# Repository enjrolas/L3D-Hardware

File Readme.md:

This repository contains all the hardware files we use to make our cubes.  It's organized in two directories 
for the two sizes of cubes we make, a 8x8x8 cube and a 16x16x16 cube.  Each directory includes the eagle files
for the baseboard that goes at the bottom of the cube, and the thin LED stick PCBs that hold the LED themselves.
The 8x8x8 cube has 64 LED sticks, and the 16x16x16 cube has a whopping 256 LED sticks.  

Electrically, the cubes are quite simple.  They're based around the popular WS2812B addressable LED and the Spark Core processor.  Our BOM
has Chinese sources, but you can also source the WS2812B LEDs from any number of sources, such as [Adafruit](https://www.adafruit.com/products/1655) and our 
friends [at Seeed Studios](http://www.seeedstudio.com/depot/WS2812B-RGB-LED-with-Integrated-Driver-Chip-10-PCs-pack-p-1675.html).
The other components are a few common passives detailed in the BOM.

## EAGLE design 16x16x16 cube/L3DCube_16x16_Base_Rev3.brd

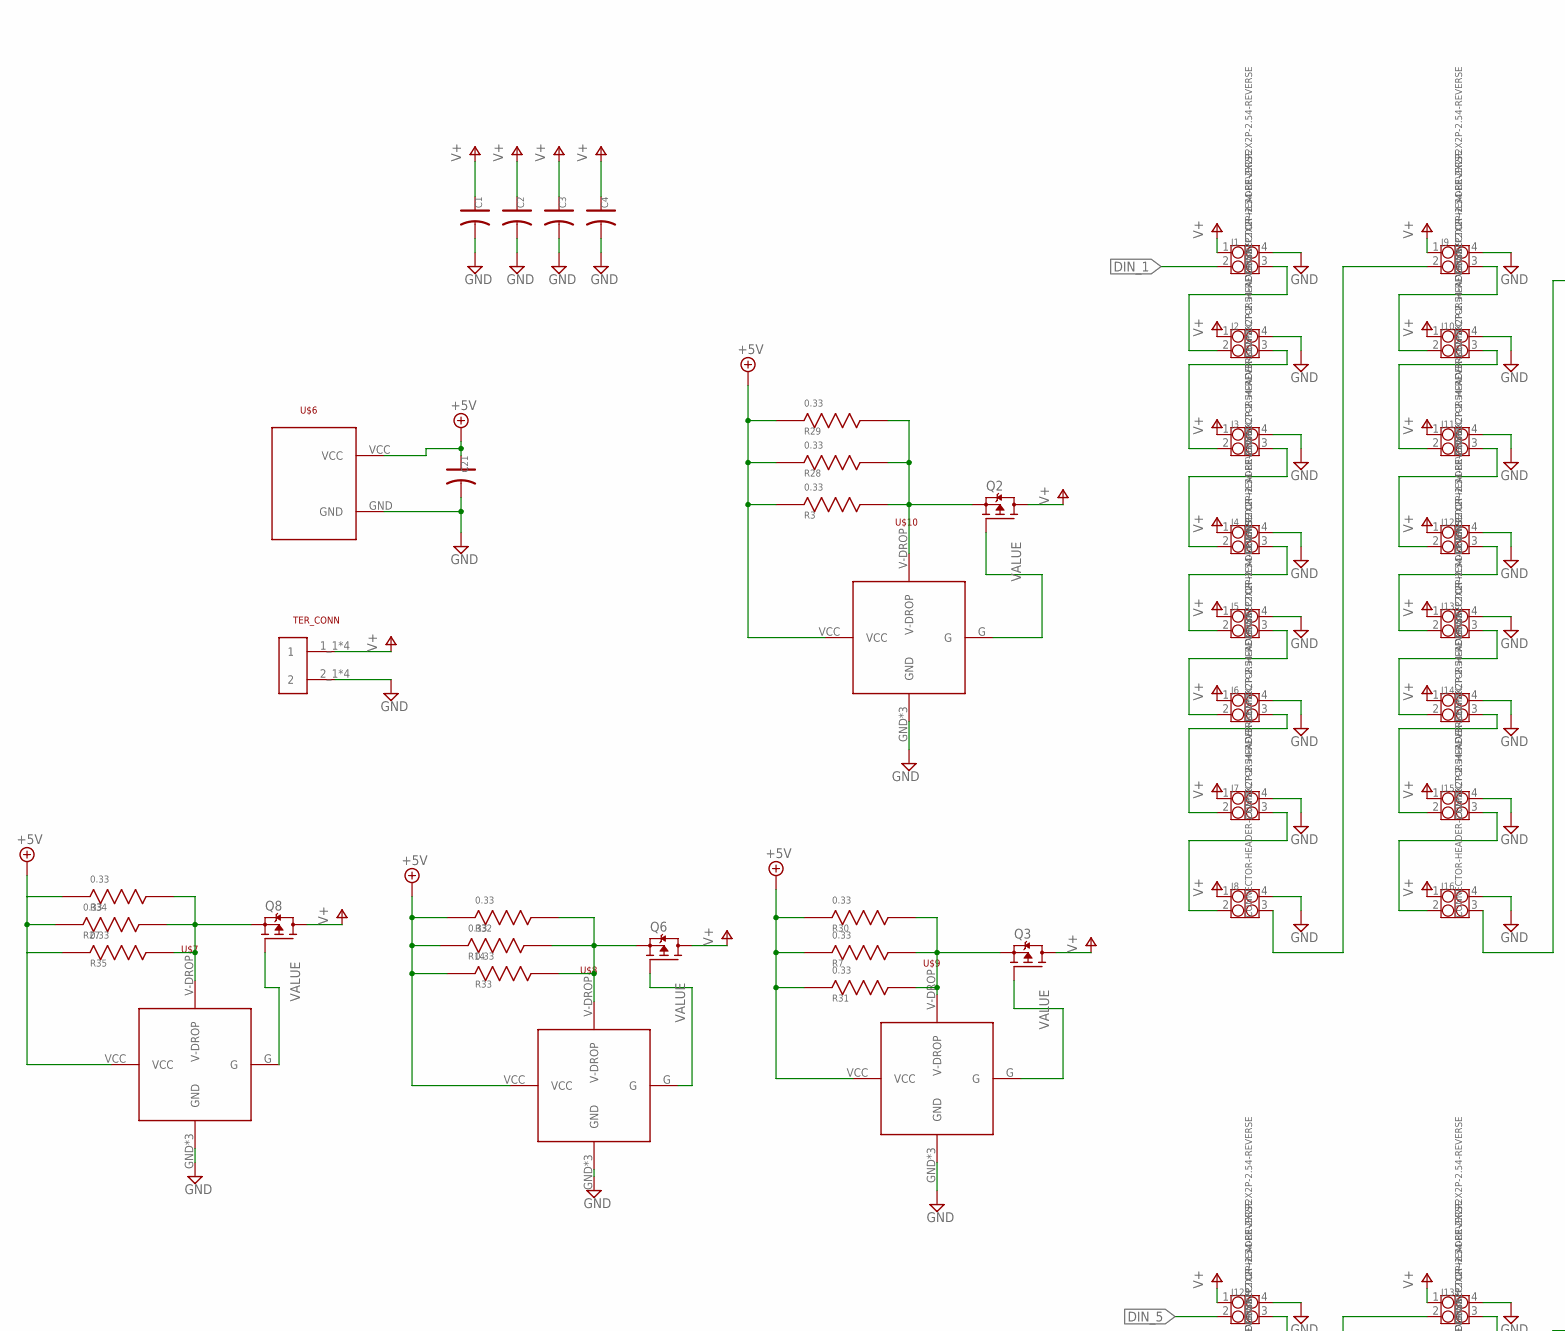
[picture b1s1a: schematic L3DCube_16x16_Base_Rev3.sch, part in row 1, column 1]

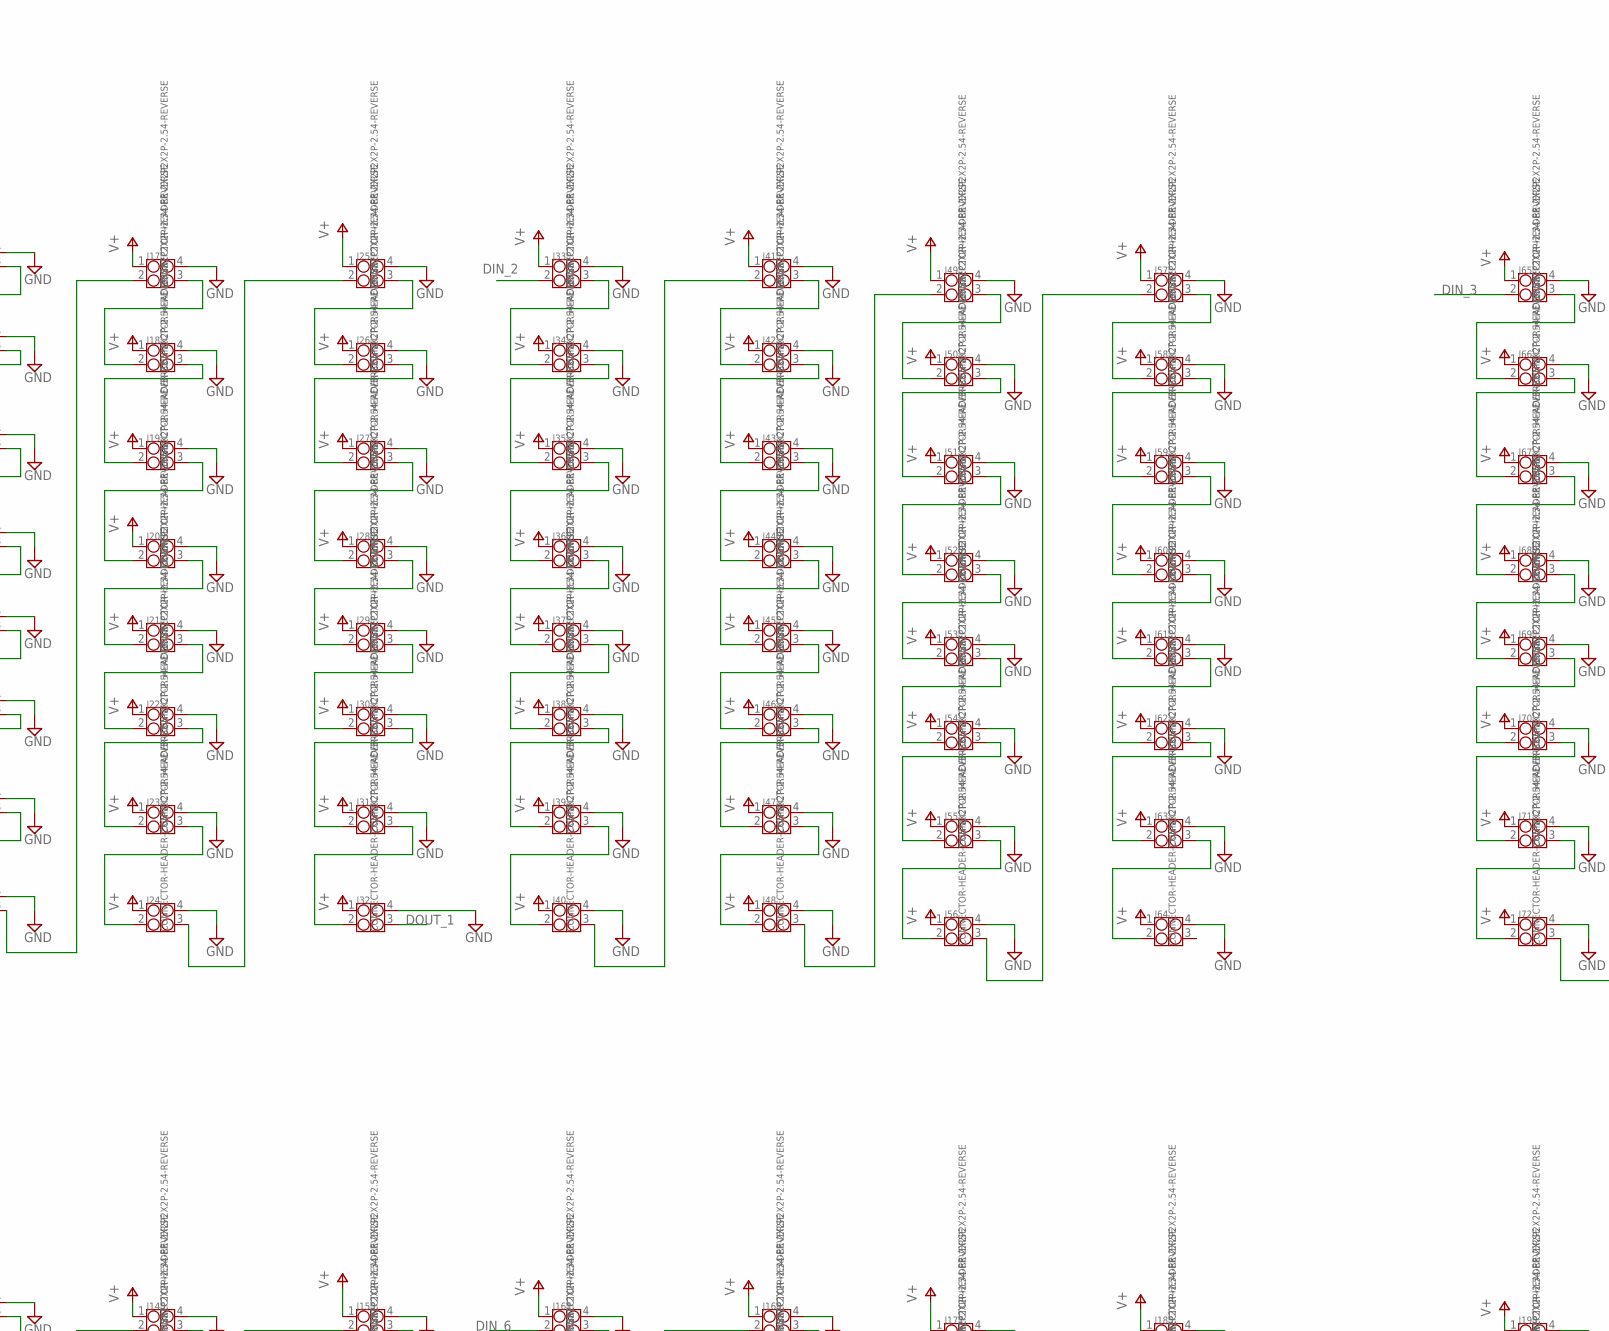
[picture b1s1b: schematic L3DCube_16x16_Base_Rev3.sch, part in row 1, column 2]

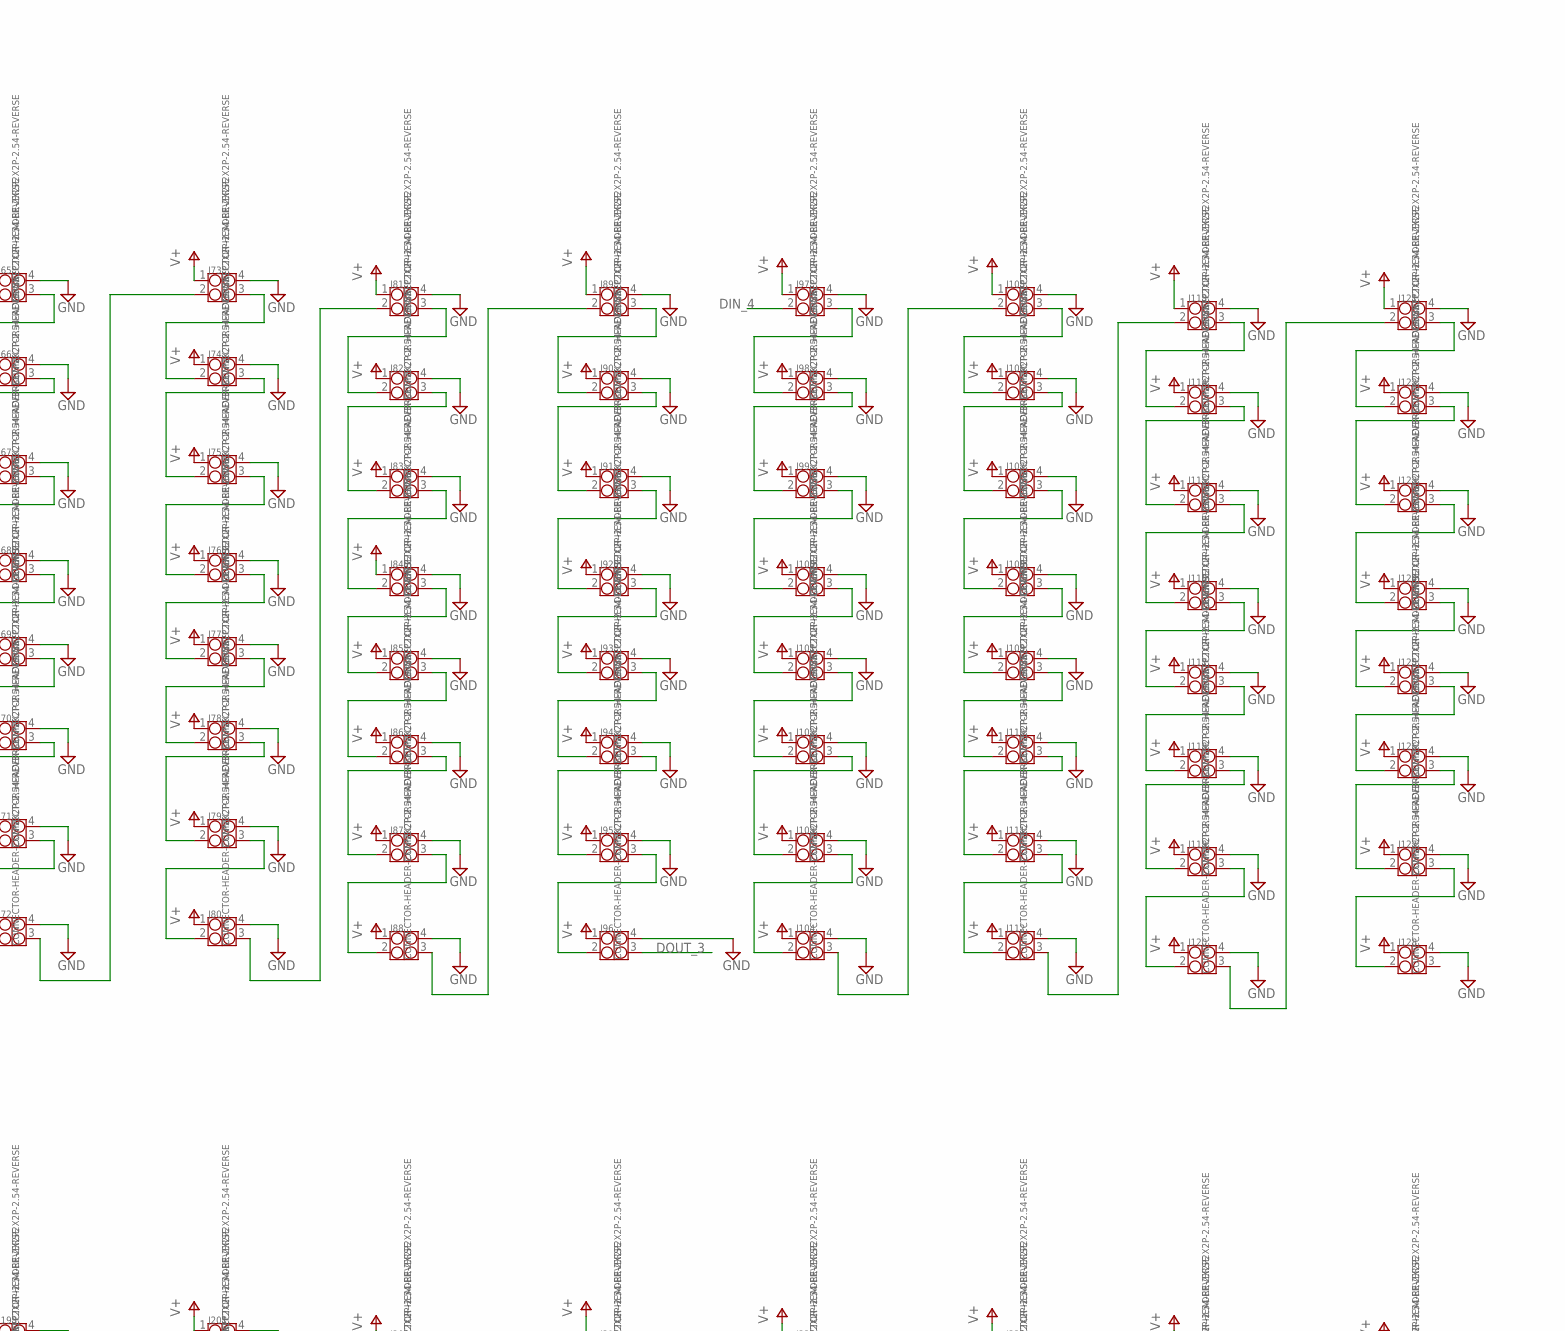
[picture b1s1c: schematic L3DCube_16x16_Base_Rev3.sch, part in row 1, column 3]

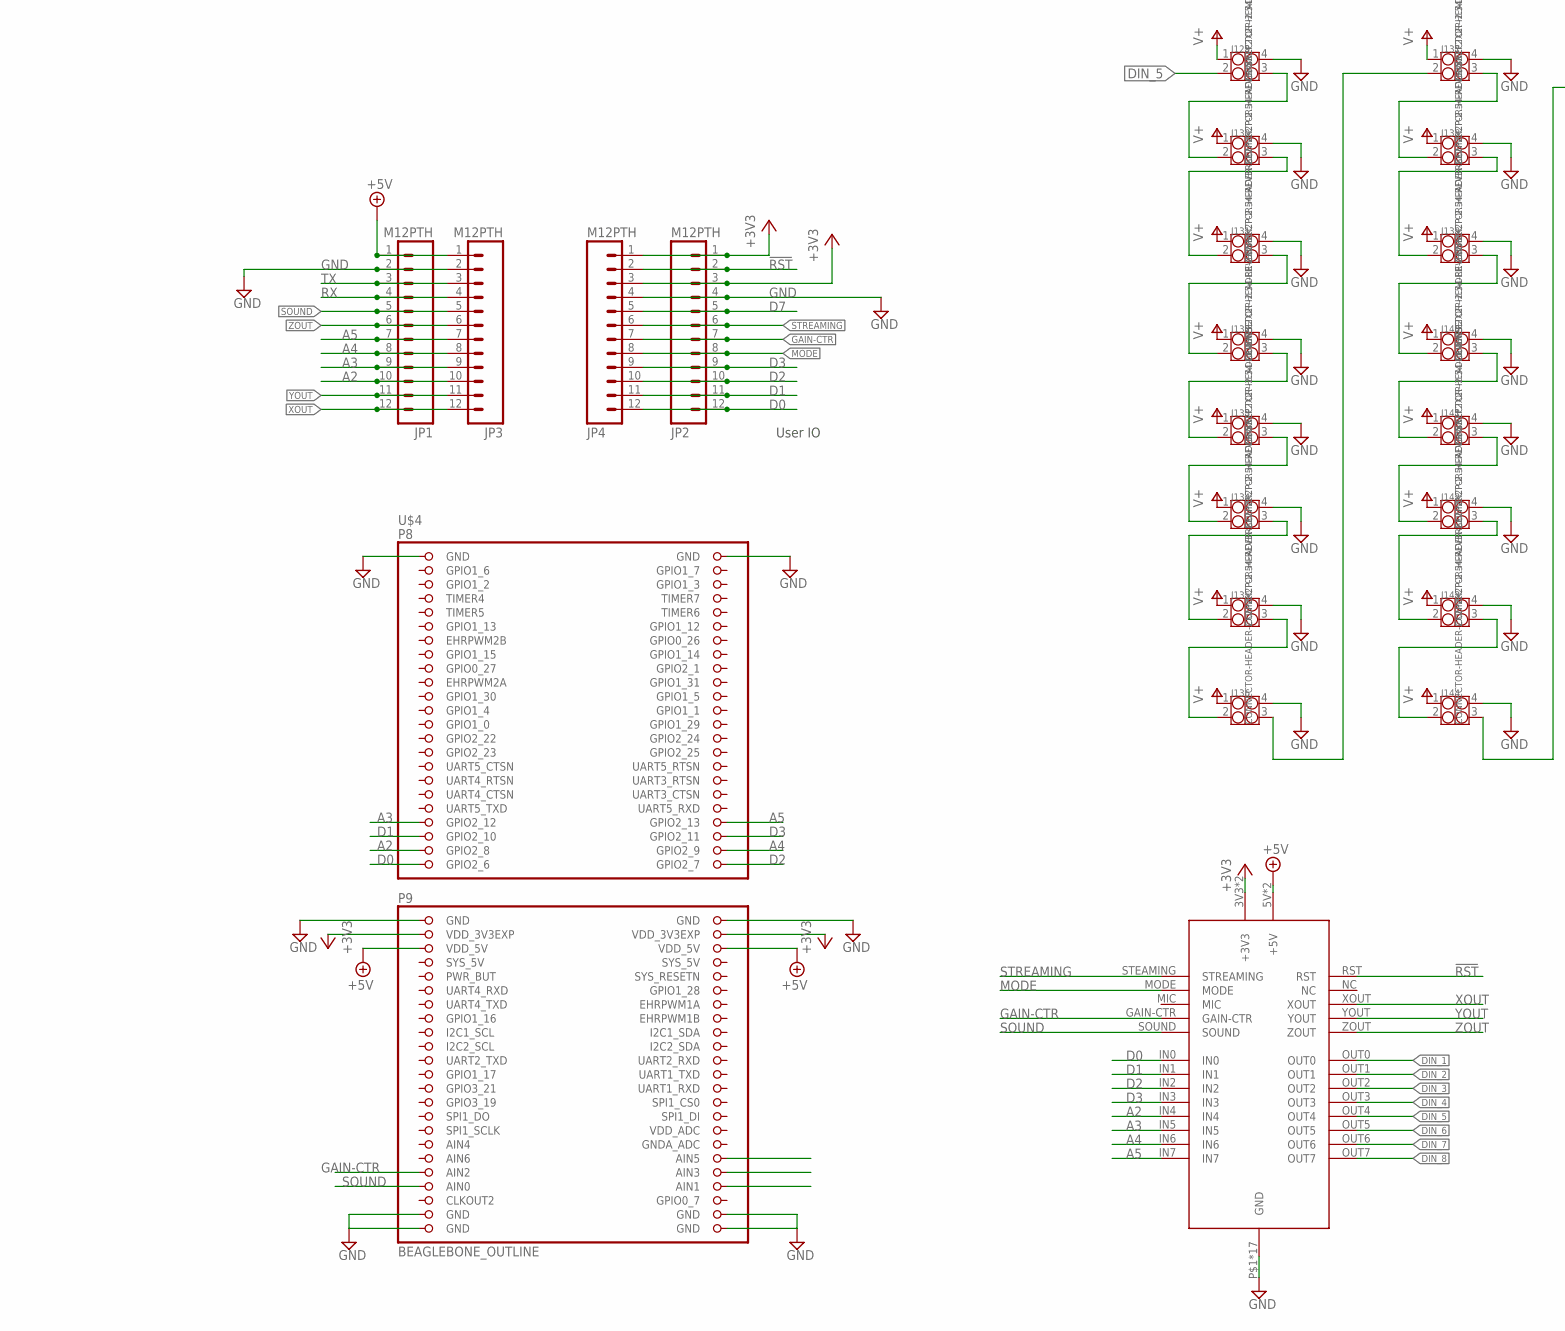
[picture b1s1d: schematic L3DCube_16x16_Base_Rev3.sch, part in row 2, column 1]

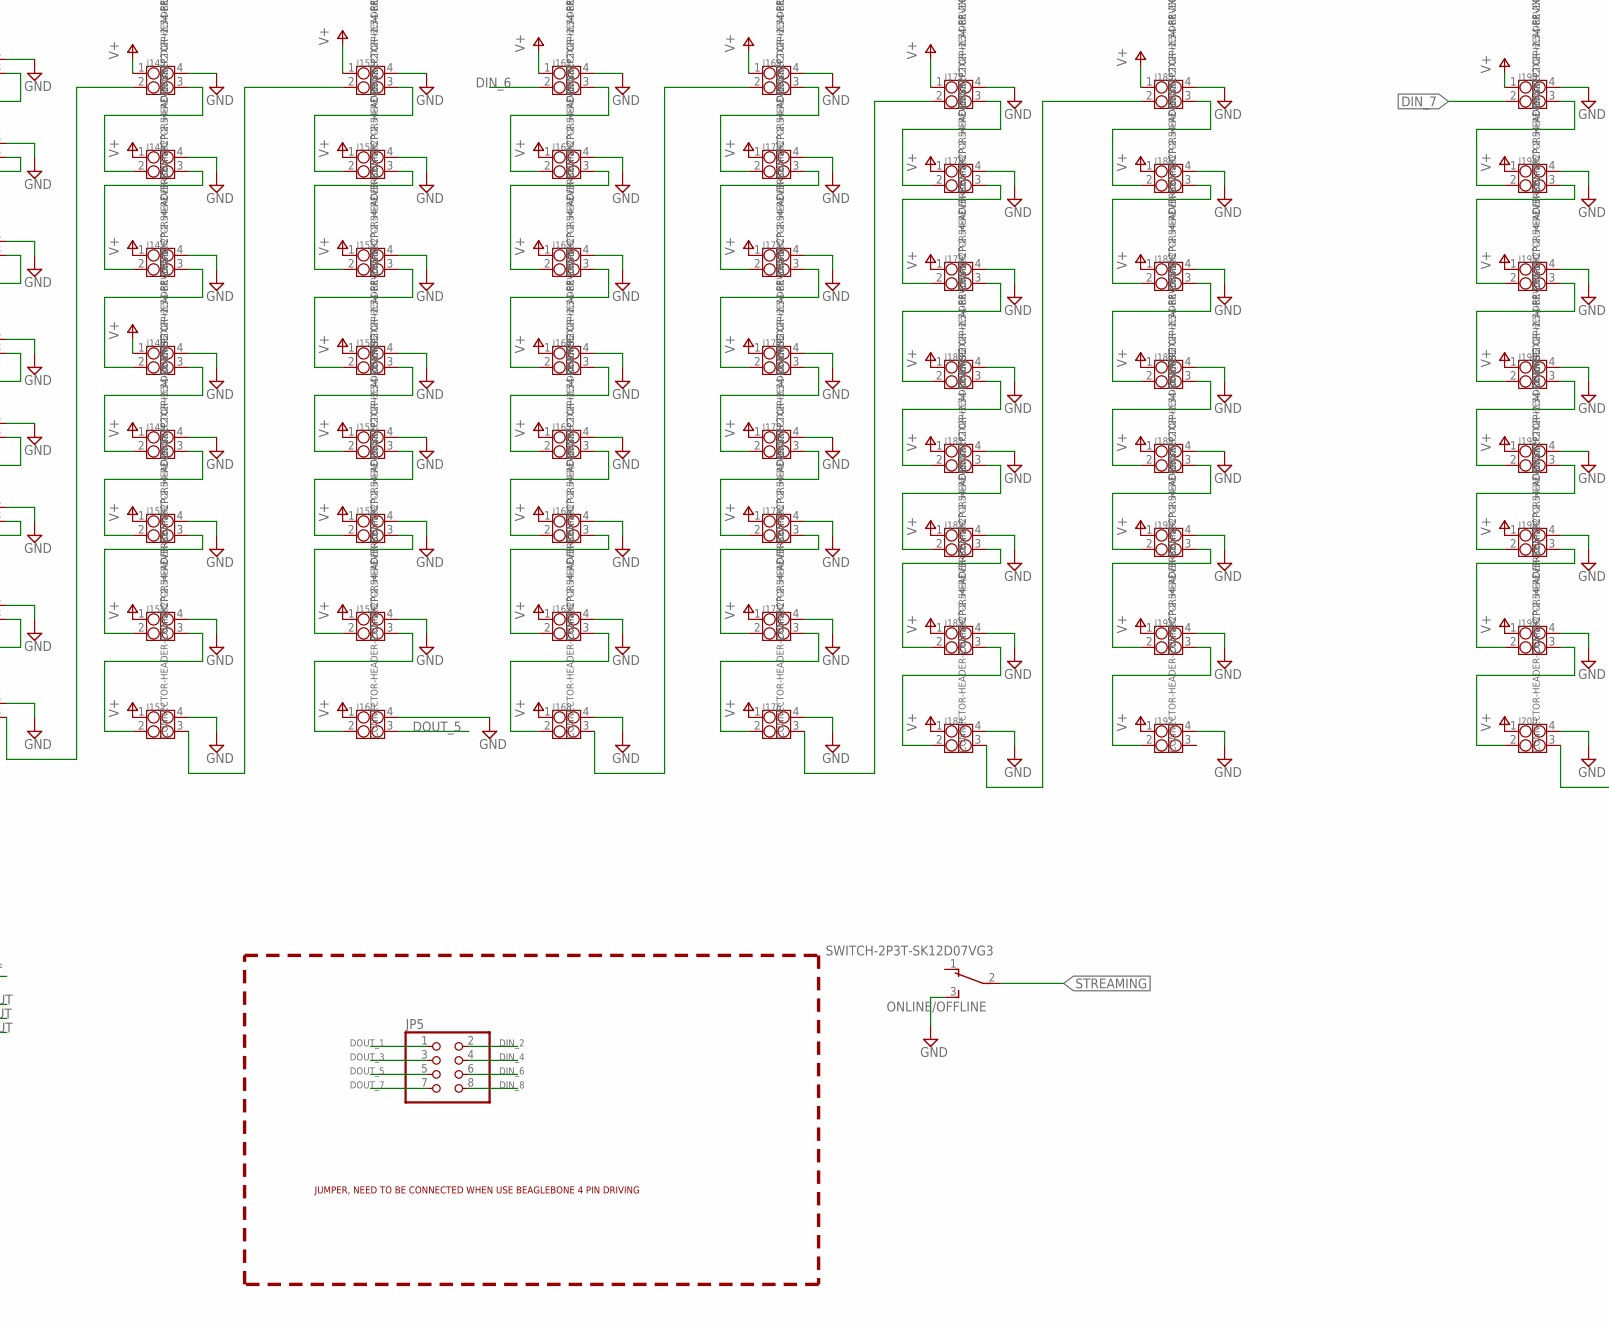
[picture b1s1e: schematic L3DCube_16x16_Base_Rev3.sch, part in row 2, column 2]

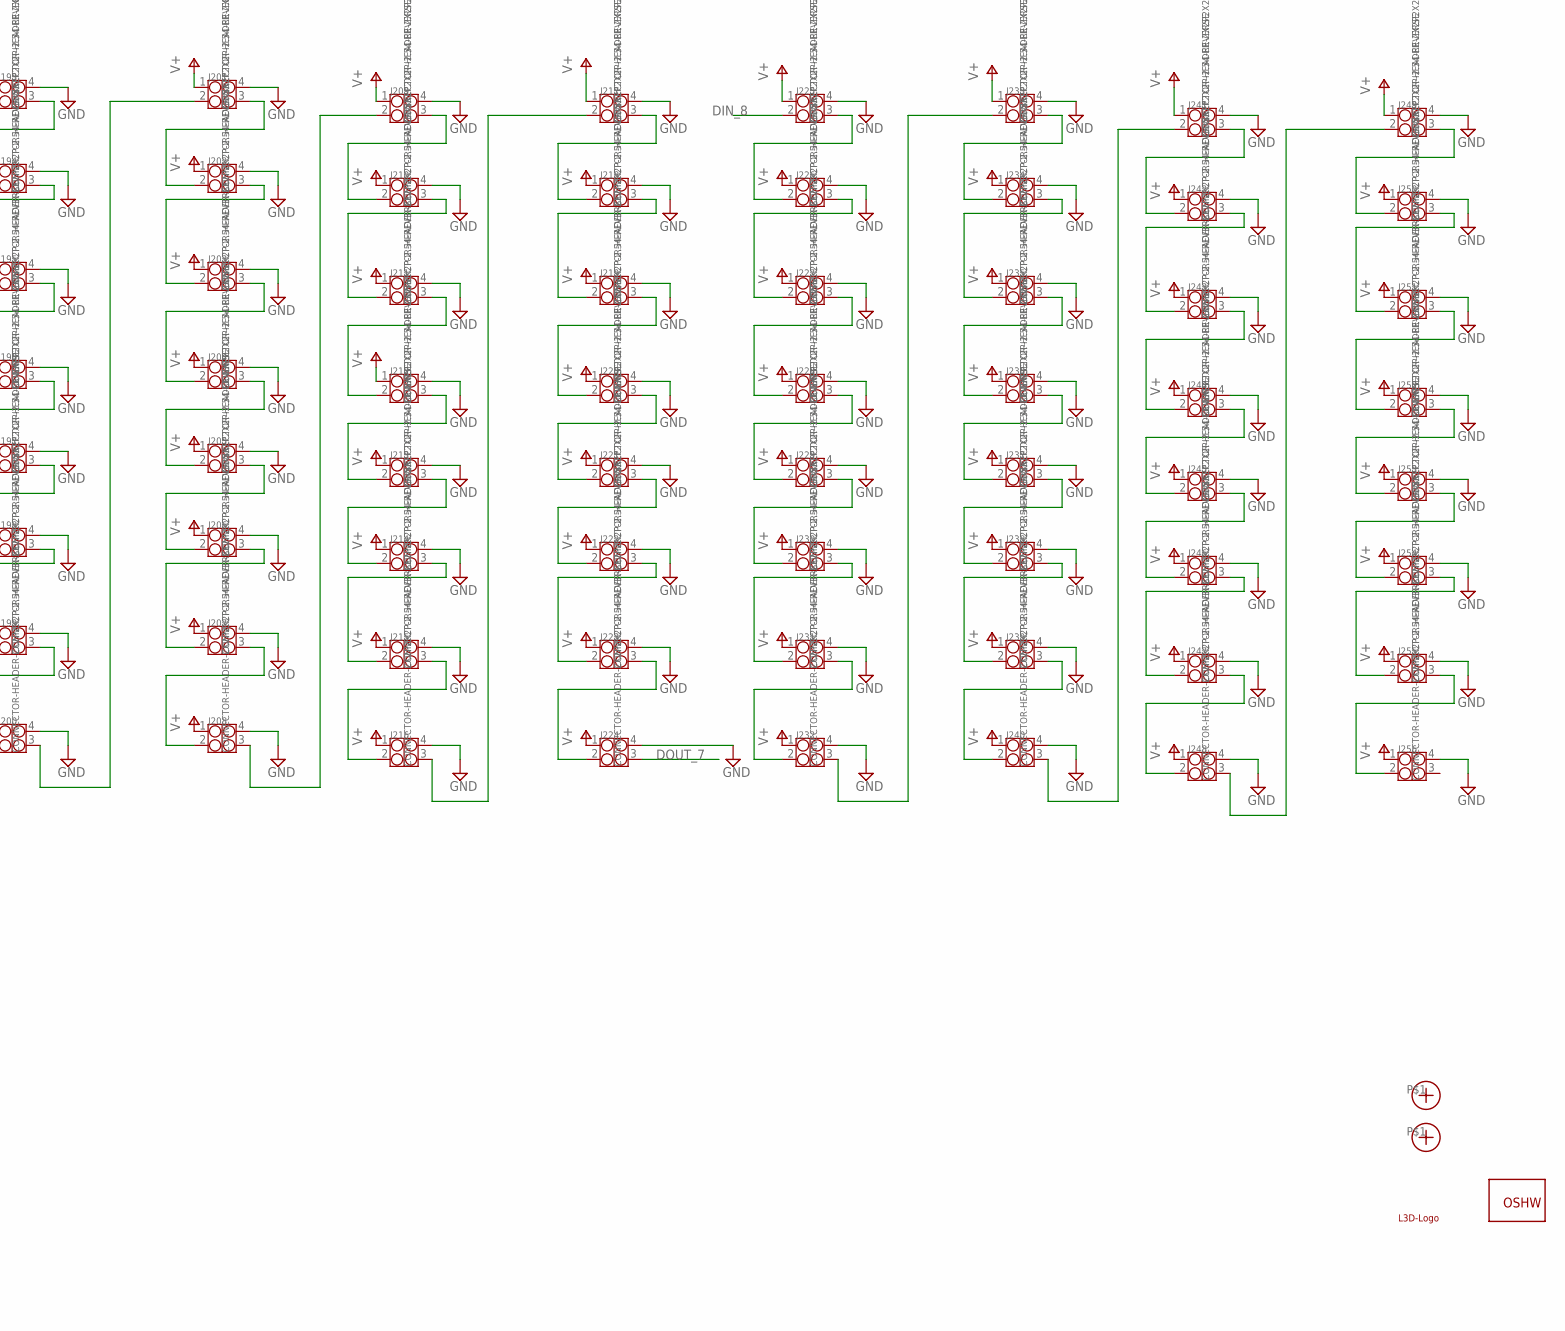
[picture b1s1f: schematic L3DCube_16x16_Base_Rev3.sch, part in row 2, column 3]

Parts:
C1, C2, C3, C4, C21: C-POLAR; CAPACITOR-E3-8
GOLD_ORB_SM1: OSHWLOGO_GOLD_ORB_LG; OSHW0
J1, J2, J3, J4, J5, J6, J7, J8, J9, J10, J11, J12, J13, J14, J15, J16, J17, J18, J19, J20, J21, J22, J23, J24, J25, J26, J27, J28, J29, J30, J31, J32, J33, J34, J35, J36, J37, J38, J39, J40, J41, J42, J43, J44, J45, J46, J47, J48, J49, J50, J51, J52, J53, J54, J55, J56, J57, J58, J59, J60, J61, J62, J63, J64, J65, J66, J67, J68, J69, J70, J71, J72, J73, J74, J75, J76, J77, J78, J79, J80, J81, J82, J83, J84, J85, J86, J87, J88, J89, J90, J91, J92, J93, J94, J95, J96, J97, J98, J99, J100, J101, J102, J103, J104, J105, J106, J107, J108, J109, J110, J111, J112, J113, J114, J115, J116, J117, J118, J119, J120, J121, J122, J123, J124, J125, J126, J127, J128, J129, J130, J131, J132, J133, J134, J135, J136, J137, J138, J139, J140, J141, J142, J143, J144, J145, J146, J147, J148, J149, J150, J151, J152, J153, J154, J155, J156, J157, J158, J159, J160, J161, J162, J163, J164, J165, J166, J167, J168, J169, J170, J171, J172, J173, J174, J175, J176, J177, J178, J179, J180, J181, J182, J183, J184, J185, J186, J187, J188, J189, J190, J191, J192, J193, J194, J195, J196, J197, J198, J199, J200, J201, J202, J203, J204, J205, J206, J207, J208, J209, J210, J211, J212, J213, J214, J215, J216, J217, J218, J219, J220, J221, J222, J223, J224, J225, J226, J227, J228, J229, J230, J231, J232, J233, J234, J235, J236, J237, J238, J239, J240, J241, J242, J243, J244, J245, J246, J247, J248, J249, J250, J251, J252, J253, J254, J255, J256: CONNECTOR-HEADER-2X2P2X2P-2.54-REVERSE; 2X2P-2.54-REVERSE
JP1, JP2, JP3, JP4: M12PTH; 1X12-SMALL-PADS
JP5: PINHD-2X4; 2X04
ONLINE/OFFLINE: SWITCH-2P3T-SK12D07VG3
Q2, Q3, Q6, Q8: FDD6637; TO252
R3, R7, R14, R27, R28, R29, R30, R31, R32, R33, R34, R35: 0.33; RESISTOR-3W-20MM
TER_CONN: TERMINAL_CONN; TERMINALCONNECTOR_15MM
U$1: L3D-LOGOL3DCUBE-LOGO-0.8X2.5; L3DCUBE-LOGO-0.8X2.5
U$2, U$3: FIDUCIAL-MARK
U$4: BEAGLEBONE_OUTLINE; BEAGLEBONE_SHIELD
U$5: CUBE-16-DAUGHTERBOARD-SOLDERPAD; CUBE-16-DAUGHTERBOARD-PAD
U$6: CONNECTOR-1X2P-POWER-PAD; 1X2P-POWER-PAD
U$7, U$8, U$9, U$10: CUBE-16-DAUGHTERBOARD-CURRENT-LMTPAD; CUBE-16-DAUGHTERBOARD-CURRENT-LMT-PAD

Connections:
!RST: JP2.2, JP4.2, U$5.RST
+3V3: JP2.1, JP2.3, JP4.1, JP4.3, U$4.49 (VDD_3V3EXP), U$4.50 (VDD_3V3EXP), U$5.3V3 (+3V3), U$5.3V3' (+3V3)
+5V: C21.+ (1), JP1.1, JP3.1, R3.1, R7.1, R14.1, R27.1, R28.1, R29.1, R30.1, R31.1, R32.1, R33.1, R34.1, R35.1, U$4.51 (VDD_5V), U$4.52 (VDD_5V), U$5.5V (+5V), U$5.5V' (+5V), U$6.VCC, U$7.VCC, U$8.VCC, U$9.VCC, U$10.VCC
A2: JP1.10, JP3.10, U$4.43 (GPIO2_8), U$5.IN4
A3: JP1.9, JP3.9, U$4.39 (GPIO2_12), U$5.IN5
A4: JP1.8, JP3.8, U$4.44 (GPIO2_9), U$5.IN6
A5: JP1.7, JP3.7, U$4.40 (GPIO2_13), U$5.IN7
D0: JP2.12, JP4.12, U$4.45 (GPIO2_6), U$5.IN0
D1: JP2.11, JP4.11, U$4.41 (GPIO2_10), U$5.IN1
D2: JP2.10, JP4.10, U$4.46 (GPIO2_7), U$5.IN2
D3: JP2.9, JP4.9, U$4.42 (GPIO2_11), U$5.IN3
D7: JP2.5, JP4.5
DIN_1: J1.2, U$5.OUT0
DIN_2: J33.2, JP5.2, U$5.OUT1
DIN_3: J65.2, U$5.OUT2
DIN_4: J97.2, JP5.4, U$5.OUT3
DIN_5: J129.2, U$5.OUT4
DIN_6: J161.2, JP5.6, U$5.OUT5
DIN_7: J193.2, U$5.OUT6
DIN_8: J225.2, JP5.8, U$5.OUT7
DOUT_1: J32.3, JP5.1
DOUT_3: J96.3, JP5.3
DOUT_5: J160.3, JP5.5
DOUT_7: J224.3, JP5.7
GAIN-CTR: JP2.7, JP4.7, U$4.83 (AIN2), U$5.GAIN-CTR
GND: C1.- (2), C2.- (2), C3.- (2), C4.- (2), C21.- (2), J1.4, J2.4, J3.4, J4.4, J5.4, J6.4, J7.4, J8.4, J9.4, J10.4, J11.4, J12.4, J13.4, J14.4, J15.4, J16.4, J17.4, J18.4, J19.4, J20.4, J21.4, J22.4, J23.4, J24.4, J25.4, J26.4, J27.4, J28.4, J29.4, J30.4, J31.4, J32.4, J33.4, J34.4, J35.4, J36.4, J37.4, J38.4, J39.4, J40.4, J41.4, J42.4, J43.4, J44.4, J45.4, J46.4, J47.4, J48.4, J49.4, J50.4, J51.4, J52.4, J53.4, J54.4, J55.4, J56.4, J57.4, J58.4, J59.4, J60.4, J61.4, J62.4, J63.4, J64.4, J65.4, J66.4, J67.4, J68.4, J69.4, J70.4, J71.4, J72.4, J73.4, J74.4, J75.4, J76.4, J77.4, J78.4, J79.4, J80.4, J81.4, J82.4, J83.4, J84.4, J85.4, J86.4, J87.4, J88.4, J89.4, J90.4, J91.4, J92.4, J93.4, J94.4, J95.4, J96.4, J97.4, J98.4, J99.4, J100.4, J101.4, J102.4, J103.4, J104.4, J105.4, J106.4, J107.4, J108.4, J109.4, J110.4, J111.4, J112.4, J113.4, J114.4, J115.4, J116.4, J117.4, J118.4, J119.4, J120.4, J121.4, J122.4, J123.4, J124.4, J125.4, J126.4, J127.4, J128.4, J129.4, J130.4, J131.4, J132.4, J133.4, J134.4, J135.4, J136.4, J137.4, J138.4, J139.4, J140.4, J141.4, J142.4, J143.4, J144.4, J145.4, J146.4, J147.4, J148.4, J149.4, J150.4, J151.4, J152.4, J153.4, J154.4, J155.4, J156.4, J157.4, J158.4, J159.4, J160.4, J161.4, J162.4, J163.4, J164.4, J165.4, J166.4, J167.4, J168.4, J169.4, J170.4, J171.4, J172.4, J173.4, J174.4, J175.4, J176.4, J177.4, J178.4, J179.4, J180.4, J181.4, J182.4, J183.4, J184.4, J185.4, J186.4, J187.4, J188.4, J189.4, J190.4, J191.4, J192.4, J193.4, J194.4, J195.4, J196.4, J197.4, J198.4, J199.4, J200.4, J201.4, J202.4, J203.4, J204.4, J205.4, J206.4, J207.4, J208.4, J209.4, J210.4, J211.4, J212.4, J213.4, J214.4, J215.4, J216.4, J217.4, J218.4, J219.4, J220.4, J221.4, J222.4, J223.4, J224.4, J225.4, J226.4, J227.4, J228.4, J229.4, J230.4, J231.4, J232.4, J233.4, J234.4, J235.4, J236.4, J237.4, J238.4, J239.4, J240.4, J241.4, J242.4, J243.4, J244.4, J245.4, J246.4, J247.4, J248.4, J249.4, J250.4, J251.4, J252.4, J253.4, J254.4, J255.4, J256.4, JP1.2, JP2.4, JP3.2, JP4.4, ONLINE/OFFLINE.3 (S), TER_CONN.2_1 (2), TER_CONN.2_2 (2), TER_CONN.2_3 (2), TER_CONN.2_4 (2), U$4.1 (GND), U$4.2 (GND), U$4.47 (GND), U$4.48 (GND), U$4.89 (GND), U$4.90 (GND), U$4.91 (GND), U$4.92 (GND), U$5.P$1 (GND), U$5.P$2 (GND), U$5.P$3 (GND), U$5.P$4 (GND), U$5.P$5 (GND), U$5.P$6 (GND), U$5.P$8 (GND), U$5.P$27 (GND), U$5.P$30 (GND), U$5.P$31 (GND), U$5.P$32 (GND), U$5.P$33 (GND), U$5.P$44 (GND), U$5.P$45 (GND), U$5.P$46 (GND), U$5.P$47 (GND), U$5.P$48 (GND), U$6.GND, U$7.GND, U$7.GND1 (GND), U$7.GND2 (GND), U$8.GND, U$8.GND1 (GND), U$8.GND2 (GND), U$9.GND, U$9.GND1 (GND), U$9.GND2 (GND), U$10.GND, U$10.GND1 (GND), U$10.GND2 (GND)
MODE: JP2.8, JP4.8, U$5.MODE
unnamed: J1.3, J2.2
unnamed: J2.3, J3.2
unnamed: J3.3, J4.2
unnamed: J5.3, J6.2
unnamed: J6.3, J7.2
unnamed: J7.3, J8.2
unnamed: J4.3, J5.2
unnamed: J9.3, J10.2
unnamed: J10.3, J11.2
unnamed: J11.3, J12.2
unnamed: J13.3, J14.2
unnamed: J14.3, J15.2
unnamed: J15.3, J16.2
unnamed: J12.3, J13.2
unnamed: J17.3, J18.2
unnamed: J18.3, J19.2
unnamed: J19.3, J20.2
unnamed: J21.3, J22.2
unnamed: J22.3, J23.2
unnamed: J23.3, J24.2
unnamed: J20.3, J21.2
unnamed: J25.3, J26.2
unnamed: J26.3, J27.2
unnamed: J27.3, J28.2
unnamed: J29.3, J30.2
unnamed: J30.3, J31.2
unnamed: J31.3, J32.2
unnamed: J28.3, J29.2
unnamed: J8.3, J9.2
unnamed: J16.3, J17.2
unnamed: J24.3, J25.2
unnamed: J65.3, J66.2
unnamed: J33.3, J34.2
unnamed: J34.3, J35.2
unnamed: J35.3, J36.2
unnamed: J37.3, J38.2
unnamed: J38.3, J39.2
unnamed: J39.3, J40.2
unnamed: J36.3, J37.2
unnamed: J41.3, J42.2
unnamed: J42.3, J43.2
unnamed: J43.3, J44.2
unnamed: J45.3, J46.2
unnamed: J46.3, J47.2
unnamed: J47.3, J48.2
unnamed: J44.3, J45.2
unnamed: J49.3, J50.2
unnamed: J50.3, J51.2
unnamed: J51.3, J52.2
unnamed: J53.3, J54.2
unnamed: J54.3, J55.2
unnamed: J55.3, J56.2
unnamed: J52.3, J53.2
unnamed: J57.3, J58.2
unnamed: J58.3, J59.2
unnamed: J59.3, J60.2
unnamed: J61.3, J62.2
unnamed: J62.3, J63.2
unnamed: J63.3, J64.2
unnamed: J60.3, J61.2
unnamed: J40.3, J41.2
unnamed: J48.3, J49.2
unnamed: J56.3, J57.2
unnamed: Q2.2 (S), R3.2, R28.2, R29.2, U$10.V-DROP
unnamed: J66.3, J67.2
unnamed: J67.3, J68.2
unnamed: J69.3, J70.2
unnamed: J70.3, J71.2
unnamed: J71.3, J72.2
unnamed: J68.3, J69.2
unnamed: J73.3, J74.2
unnamed: J74.3, J75.2
unnamed: J75.3, J76.2
unnamed: J77.3, J78.2
unnamed: J78.3, J79.2
unnamed: J79.3, J80.2
unnamed: J76.3, J77.2
unnamed: J81.3, J82.2
unnamed: J82.3, J83.2
unnamed: J83.3, J84.2
unnamed: J85.3, J86.2
unnamed: J86.3, J87.2
unnamed: J87.3, J88.2
unnamed: J84.3, J85.2
unnamed: J89.3, J90.2
unnamed: J90.3, J91.2
unnamed: J91.3, J92.2
unnamed: J93.3, J94.2
unnamed: J94.3, J95.2
unnamed: J95.3, J96.2
unnamed: J92.3, J93.2
unnamed: J72.3, J73.2
unnamed: J80.3, J81.2
unnamed: J88.3, J89.2
unnamed: J97.3, J98.2
unnamed: J98.3, J99.2
unnamed: J99.3, J100.2
unnamed: J101.3, J102.2
unnamed: J102.3, J103.2
unnamed: J103.3, J104.2
unnamed: J100.3, J101.2
unnamed: J105.3, J106.2
unnamed: J106.3, J107.2
unnamed: J107.3, J108.2
unnamed: J109.3, J110.2
unnamed: J110.3, J111.2
unnamed: J111.3, J112.2
unnamed: J108.3, J109.2
unnamed: J113.3, J114.2
unnamed: J114.3, J115.2
unnamed: J115.3, J116.2
unnamed: J117.3, J118.2
unnamed: J118.3, J119.2
unnamed: J119.3, J120.2
unnamed: J116.3, J117.2
unnamed: J121.3, J122.2
unnamed: J122.3, J123.2
unnamed: J123.3, J124.2
unnamed: J125.3, J126.2
unnamed: J126.3, J127.2
unnamed: J127.3, J128.2
unnamed: J124.3, J125.2
unnamed: J104.3, J105.2
unnamed: J112.3, J113.2
unnamed: J120.3, J121.2
unnamed: Q2.1 (G), U$10.G
unnamed: J129.3, J130.2
unnamed: J130.3, J131.2
unnamed: J131.3, J132.2
unnamed: J133.3, J134.2
unnamed: J134.3, J135.2
unnamed: J135.3, J136.2
unnamed: J132.3, J133.2
unnamed: J137.3, J138.2
unnamed: J138.3, J139.2
unnamed: J139.3, J140.2
unnamed: J141.3, J142.2
unnamed: J142.3, J143.2
unnamed: J143.3, J144.2
unnamed: J140.3, J141.2
unnamed: J145.3, J146.2
unnamed: J146.3, J147.2
unnamed: J147.3, J148.2
unnamed: J149.3, J150.2
unnamed: J150.3, J151.2
unnamed: J151.3, J152.2
unnamed: J148.3, J149.2
unnamed: J153.3, J154.2
unnamed: J154.3, J155.2
unnamed: J155.3, J156.2
unnamed: J157.3, J158.2
unnamed: J158.3, J159.2
unnamed: J159.3, J160.2
unnamed: J156.3, J157.2
unnamed: J136.3, J137.2
unnamed: J144.3, J145.2
unnamed: J152.3, J153.2
unnamed: J161.3, J162.2
unnamed: J162.3, J163.2
unnamed: J163.3, J164.2
unnamed: J165.3, J166.2
unnamed: J166.3, J167.2
unnamed: J167.3, J168.2
unnamed: J164.3, J165.2
unnamed: J169.3, J170.2
unnamed: J170.3, J171.2
unnamed: J171.3, J172.2
unnamed: J173.3, J174.2
unnamed: J174.3, J175.2
unnamed: J175.3, J176.2
unnamed: J172.3, J173.2
unnamed: J177.3, J178.2
unnamed: J178.3, J179.2
unnamed: J179.3, J180.2
unnamed: J181.3, J182.2
unnamed: J182.3, J183.2
unnamed: J183.3, J184.2
unnamed: J180.3, J181.2
unnamed: J185.3, J186.2
unnamed: J186.3, J187.2
unnamed: J187.3, J188.2
unnamed: J189.3, J190.2
unnamed: J190.3, J191.2
unnamed: J191.3, J192.2
unnamed: J188.3, J189.2
unnamed: J168.3, J169.2
unnamed: J176.3, J177.2
unnamed: J184.3, J185.2
unnamed: Q3.2 (S), R7.2, R30.2, R31.2, U$9.V-DROP
unnamed: J193.3, J194.2
unnamed: J194.3, J195.2
unnamed: J195.3, J196.2
unnamed: J197.3, J198.2
unnamed: J198.3, J199.2
unnamed: J199.3, J200.2
unnamed: J196.3, J197.2
unnamed: J201.3, J202.2
unnamed: J202.3, J203.2
unnamed: J203.3, J204.2
unnamed: J205.3, J206.2
unnamed: J206.3, J207.2
unnamed: J207.3, J208.2
unnamed: J204.3, J205.2
unnamed: J209.3, J210.2
unnamed: J210.3, J211.2
unnamed: J211.3, J212.2
unnamed: J213.3, J214.2
unnamed: J214.3, J215.2
unnamed: J215.3, J216.2
unnamed: J212.3, J213.2
unnamed: J217.3, J218.2
unnamed: J218.3, J219.2
unnamed: J219.3, J220.2
unnamed: J221.3, J222.2
unnamed: J222.3, J223.2
unnamed: J223.3, J224.2
unnamed: J220.3, J221.2
unnamed: J200.3, J201.2
unnamed: J208.3, J209.2
unnamed: J216.3, J217.2
unnamed: J225.3, J226.2
unnamed: J226.3, J227.2
unnamed: J227.3, J228.2
unnamed: J229.3, J230.2
unnamed: J230.3, J231.2
unnamed: J231.3, J232.2
unnamed: J228.3, J229.2
unnamed: J233.3, J234.2
unnamed: J234.3, J235.2
unnamed: J235.3, J236.2
unnamed: J237.3, J238.2
unnamed: J238.3, J239.2
unnamed: J239.3, J240.2
unnamed: J236.3, J237.2
unnamed: J241.3, J242.2
unnamed: J242.3, J243.2
unnamed: J243.3, J244.2
unnamed: J245.3, J246.2
unnamed: J246.3, J247.2
unnamed: J247.3, J248.2
unnamed: J244.3, J245.2
unnamed: J249.3, J250.2
unnamed: J250.3, J251.2
unnamed: J251.3, J252.2
unnamed: J253.3, J254.2
unnamed: J254.3, J255.2
unnamed: J255.3, J256.2
unnamed: J252.3, J253.2
unnamed: J232.3, J233.2
unnamed: J240.3, J241.2
unnamed: J248.3, J249.2
unnamed: Q3.1 (G), U$9.G
unnamed: Q8.1 (G), U$7.G
unnamed: Q6.1 (G), U$8.G
unnamed: Q6.2 (S), R14.2, R32.2, R33.2, U$8.V-DROP
unnamed: Q8.2 (S), R27.2, R34.2, R35.2, U$7.V-DROP
RX: JP1.4, JP3.4
SOUND: JP1.5, JP3.5, U$4.85 (AIN0), U$5.SOUND
STREAMING: JP2.6, JP4.6, ONLINE/OFFLINE.2, U$5.STEAMING (STREAMING)
SYS_5V: U$4.53 (SYS_5V)
TX: JP1.3, JP3.3
V+: C1.+ (1), C2.+ (1), C3.+ (1), C4.+ (1), J1.1, J2.1, J3.1, J4.1, J5.1, J6.1, J7.1, J8.1, J9.1, J10.1, J11.1, J12.1, J13.1, J14.1, J15.1, J16.1, J17.1, J18.1, J19.1, J20.1, J21.1, J22.1, J23.1, J24.1, J25.1, J26.1, J27.1, J28.1, J29.1, J30.1, J31.1, J32.1, J33.1, J34.1, J35.1, J36.1, J37.1, J38.1, J39.1, J40.1, J41.1, J42.1, J43.1, J44.1, J45.1, J46.1, J47.1, J48.1, J49.1, J50.1, J51.1, J52.1, J53.1, J54.1, J55.1, J56.1, J57.1, J58.1, J59.1, J60.1, J61.1, J62.1, J63.1, J64.1, J65.1, J66.1, J67.1, J68.1, J69.1, J70.1, J71.1, J72.1, J73.1, J74.1, J75.1, J76.1, J77.1, J78.1, J79.1, J80.1, J81.1, J82.1, J83.1, J84.1, J85.1, J86.1, J87.1, J88.1, J89.1, J90.1, J91.1, J92.1, J93.1, J94.1, J95.1, J96.1, J97.1, J98.1, J99.1, J100.1, J101.1, J102.1, J103.1, J104.1, J105.1, J106.1, J107.1, J108.1, J109.1, J110.1, J111.1, J112.1, J113.1, J114.1, J115.1, J116.1, J117.1, J118.1, J119.1, J120.1, J121.1, J122.1, J123.1, J124.1, J125.1, J126.1, J127.1, J128.1, J129.1, J130.1, J131.1, J132.1, J133.1, J134.1, J135.1, J136.1, J137.1, J138.1, J139.1, J140.1, J141.1, J142.1, J143.1, J144.1, J145.1, J146.1, J147.1, J148.1, J149.1, J150.1, J151.1, J152.1, J153.1, J154.1, J155.1, J156.1, J157.1, J158.1, J159.1, J160.1, J161.1, J162.1, J163.1, J164.1, J165.1, J166.1, J167.1, J168.1, J169.1, J170.1, J171.1, J172.1, J173.1, J174.1, J175.1, J176.1, J177.1, J178.1, J179.1, J180.1, J181.1, J182.1, J183.1, J184.1, J185.1, J186.1, J187.1, J188.1, J189.1, J190.1, J191.1, J192.1, J193.1, J194.1, J195.1, J196.1, J197.1, J198.1, J199.1, J200.1, J201.1, J202.1, J203.1, J204.1, J205.1, J206.1, J207.1, J208.1, J209.1, J210.1, J211.1, J212.1, J213.1, J214.1, J215.1, J216.1, J217.1, J218.1, J219.1, J220.1, J221.1, J222.1, J223.1, J224.1, J225.1, J226.1, J227.1, J228.1, J229.1, J230.1, J231.1, J232.1, J233.1, J234.1, J235.1, J236.1, J237.1, J238.1, J239.1, J240.1, J241.1, J242.1, J243.1, J244.1, J245.1, J246.1, J247.1, J248.1, J249.1, J250.1, J251.1, J252.1, J253.1, J254.1, J255.1, J256.1, Q2.3 (D), Q3.3 (D), Q6.3 (D), Q8.3 (D), TER_CONN.1_1 (1), TER_CONN.1_2 (1), TER_CONN.1_3 (1), TER_CONN.1_4 (1)
XOUT: JP1.12, JP3.12, U$4.86 (AIN1), U$5.XOUT
YOUT: JP1.11, JP3.11, U$4.84 (AIN3), U$5.YOUT
ZOUT: JP1.6, JP3.6, U$4.82 (AIN5), U$5.ZOUT

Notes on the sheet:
User IO
JUMPER, NEED TO BE CONNECTED WHEN USE BEAGLEBONE 4 PIN DRIVING
